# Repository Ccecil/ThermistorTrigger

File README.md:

# ThermistorTrigger

Setpoint trigger designed to be a hardware failsafe for thermistor based temperature readings

This is designed to be a trigger board that can trigger other devices in the event of an overtemperature.  

Simply plug a standard thermistor into either input then the signal is buffered by an opamp and stabilized.  From there you can take the signal out and send it to your main control board as a temp sensor but it also drives into another opamp setpoint trigger which is set by the onboard potentiometer.  This allows you to set a trigger point in hardware that will drive the digital output of the setpoint trigger low if it exceeds the desired temp.

This is intended to go along with a couple of my other projects (Flambehub and Flambegate which are the devices which will kill the power in a "dumb" way requiring no MCU intervention) but this can also be used on a device such as a 3d printer (or other CNC device) to trigger a halt on the MCU if it is attached to the control board.

Available at: https://www.robosprout.com/product/thermistortrigger/

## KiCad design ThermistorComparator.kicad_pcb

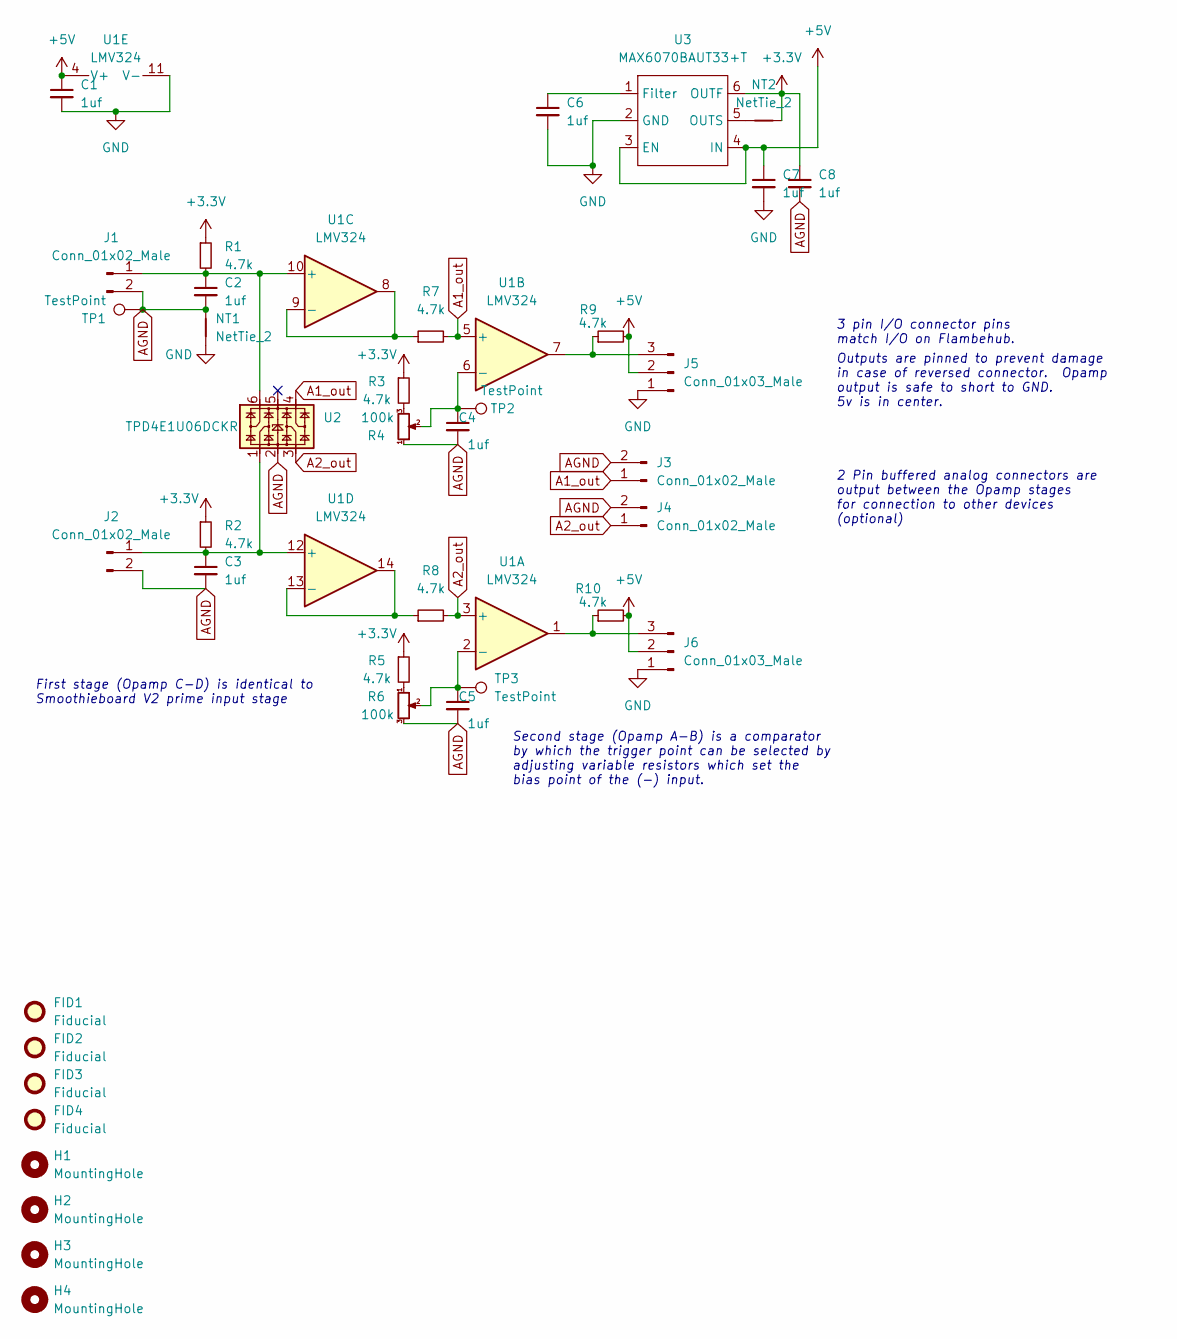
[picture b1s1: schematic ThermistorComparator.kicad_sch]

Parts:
C1, C2, C3, C4, C5, C6, C7, C8: 1uf; C_0402_1005Metric
FID1, FID2, FID3, FID4: Fiducial; Fiducial_0.5mm_Mask1mm
H1, H2, H3, H4: MountingHole; MountingHole_2.5mm
J1, J2, J3, J4: Conn_01x02_Male; Molex_KK-254_AE-6410-02A_1x02_P2.54mm_Vertical
J5, J6: Conn_01x03_Male; Molex_KK-254_AE-6410-03A_1x03_P2.54mm_Vertical
NT1, NT2: NetTie_2; NetTie-2_SMD_Pad0.5mm
R1, R2, R3, R5, R7, R8, R9, R10: 4.7k; R_0402_1005Metric
R4, R6: 100k; Potentiometer_Bourns_TC33X_Vertical
TP1, TP2, TP3: TestPoint; TestPoint_THTPad_1.0x1.0mm_Drill0.5mm
U1: LMV324; TSSOP-14_4.4x5mm_P0.65mm
U2: TPD4E1U06DCKR; SOT-363_SC-70-6
U3: MAX6070BAUT33+T; SOT-23-6

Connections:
+3.3V: C8.1, NT2.1, R1.1, R2.1, R3.1, R5.1, U3.6 (OUTF)
+5V: C1.1, C7.1, J5.2, J6.2, R9.2, R10.2, U1.4 (V+), U3.3 (EN), U3.4 (IN)
A1_out: J3.1, R7.2, U1.5 (+), U2.4
A2_out: J4.1, R8.2, U1.3 (+), U2.3
AGND: C2.2, C3.2, C4.2, C5.2, C8.2, J1.2, J2.2, J3.2, J4.2, NT1.2, R4.1, R6.3, TP1.1, U2.2
GND: C1.2, C6.2, C7.2, J5.1, J6.1, NT1.1, U1.11 (V-), U3.2 (GND)
unnamed: C2.1, J1.1, R1.2, U1.10 (+), U2.6
unnamed: C3.1, J2.1, R2.2, U1.12 (+), U2.1
unnamed: C4.1, R4.2, TP2.1, U1.6 (-)
unnamed: C5.1, R6.2, TP3.1, U1.2 (-)
unnamed: C6.1, U3.1 (Filter)
unnamed: J5.3, R9.1, U1.7
unnamed: J6.3, R10.1, U1.1
unnamed: NT2.2, U3.5 (OUTS)
unnamed: R3.2, R4.3
unnamed: R5.2, R6.1
unnamed: R7.1, U1.8, U1.9 (-)
unnamed: R8.1, U1.13 (-), U1.14

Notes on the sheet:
2 Pin buffered analog connectors are output between the Opamp stages for connection to other devices (optional)
First stage (Opamp C-D) is identical to Smoothieboard V2 prime input stage
Outputs are pinned to prevent damage in case of reversed connector. Opamp output is safe to short to GND. 5v is in center.
3 pin I/O connector pins match I/O on Flambehub.
Second stage (Opamp A-B) is a comparator by which the trigger point can be selected by adjusting variable resistors which set the bias point of the (-) input.

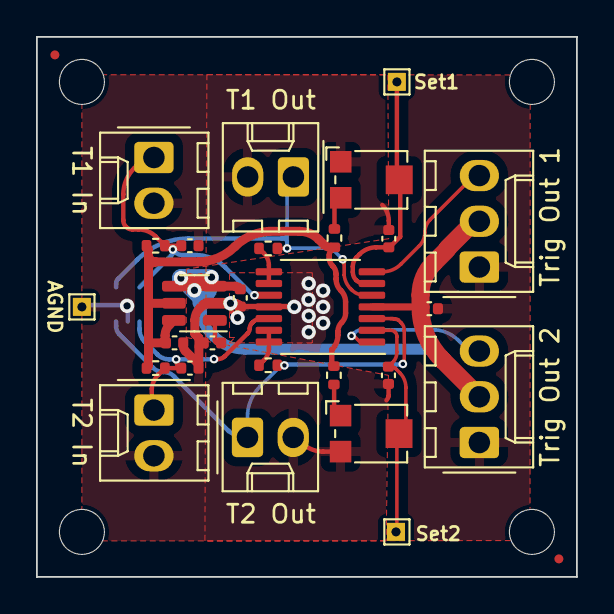
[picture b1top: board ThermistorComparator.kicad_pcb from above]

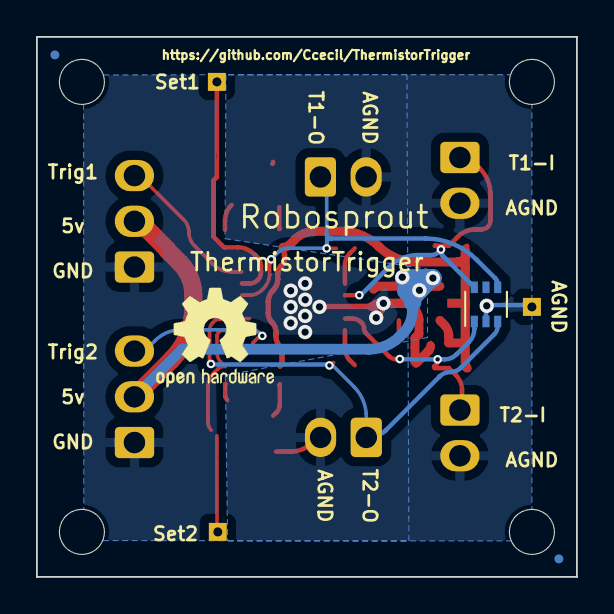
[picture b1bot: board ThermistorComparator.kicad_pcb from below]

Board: 2 copper layers, 30.0 x 30.0 mm, 38 parts (3 on the bottom side), 18 nets.

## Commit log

2023-11-13 Upload files
